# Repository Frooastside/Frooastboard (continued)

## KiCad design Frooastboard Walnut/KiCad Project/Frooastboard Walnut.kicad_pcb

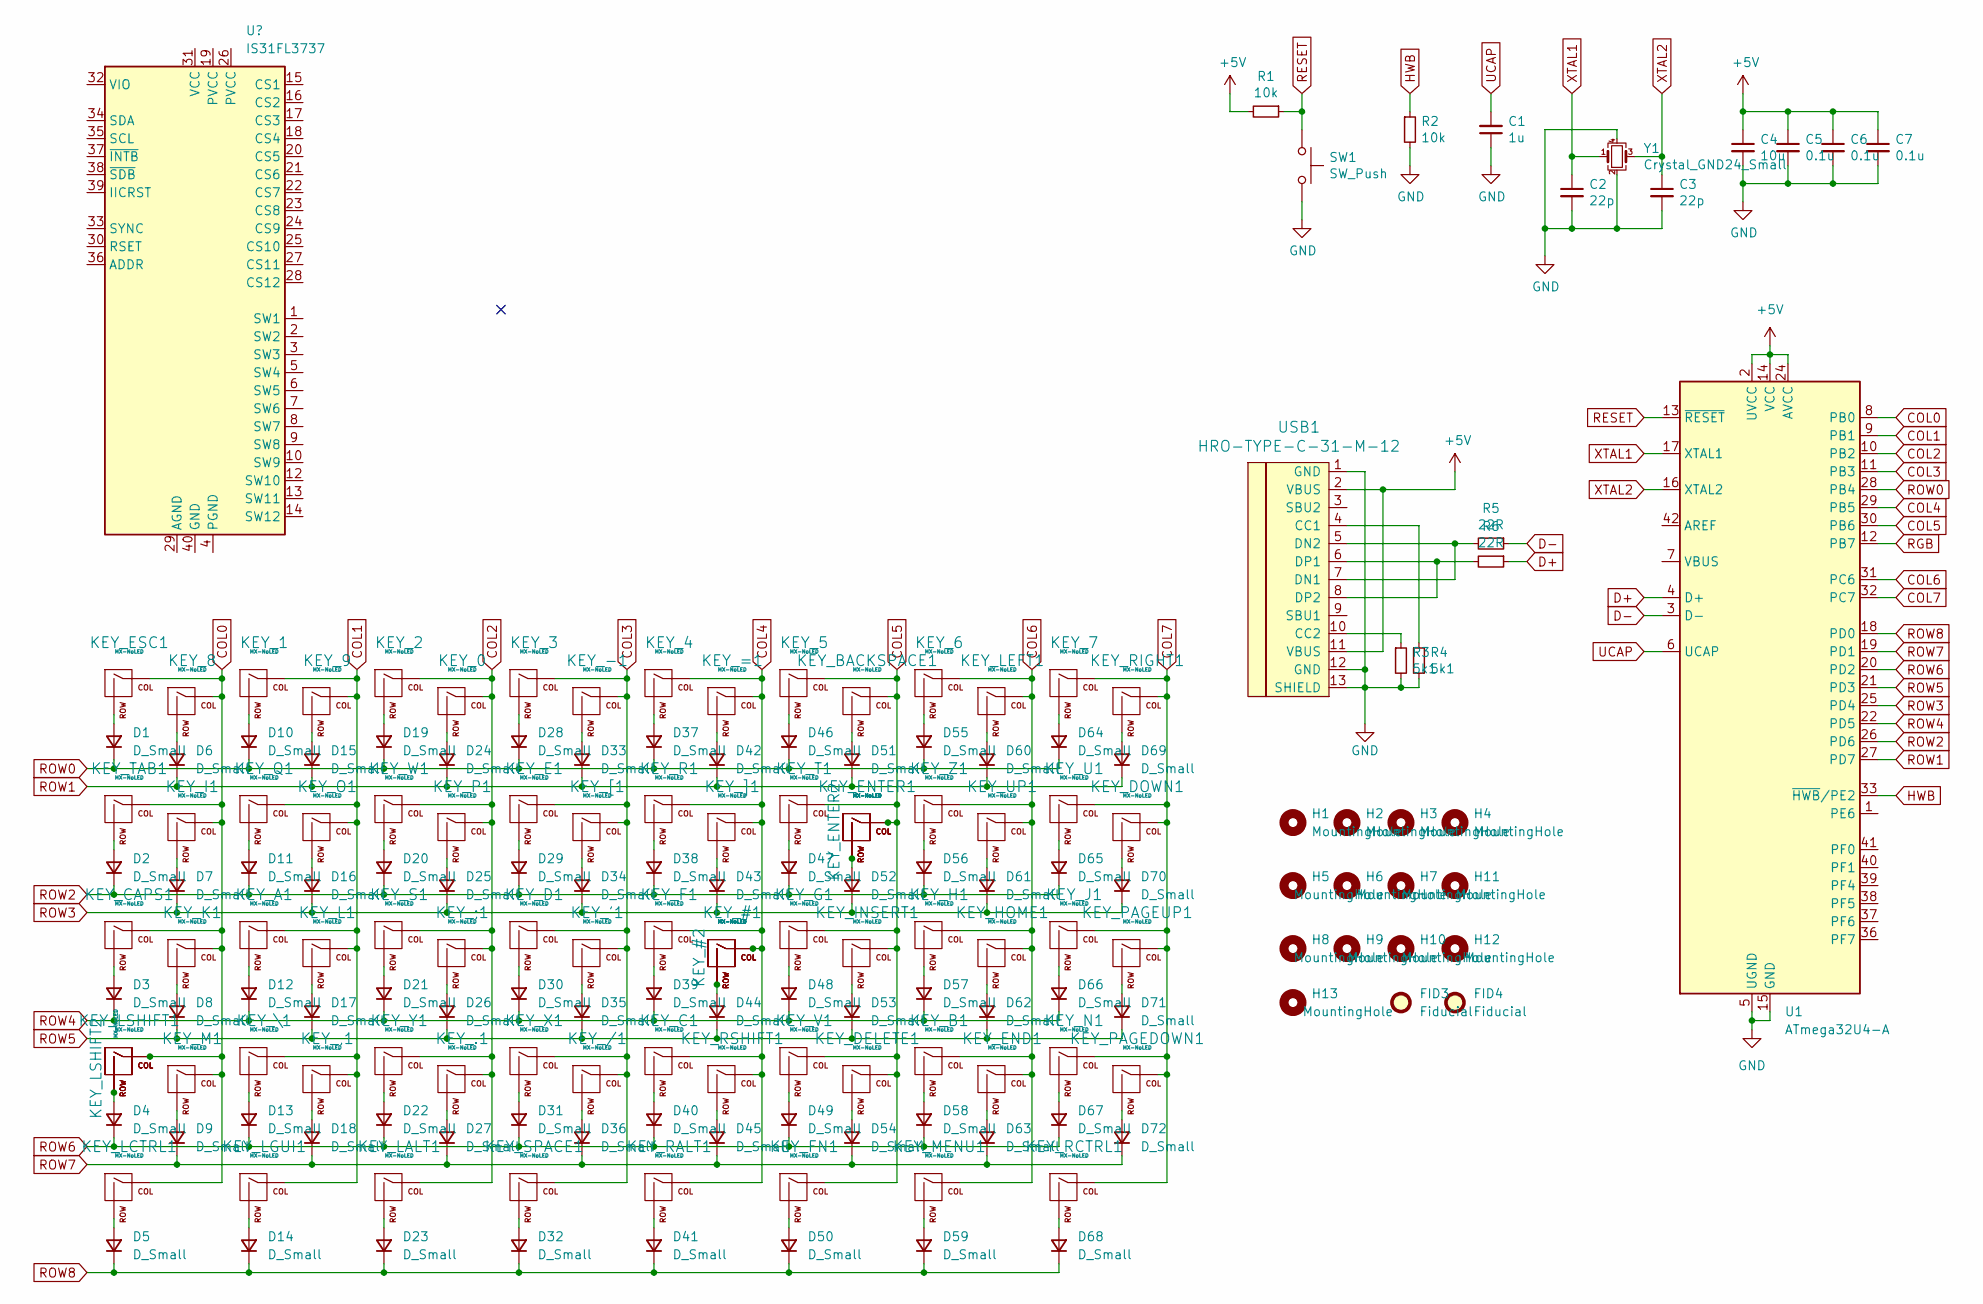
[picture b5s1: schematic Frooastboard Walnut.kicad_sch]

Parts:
C1: 1u; C_0805_2012Metric
C2, C3: 22p; C_0805_2012Metric
C4: 10u; C_0805_2012Metric
C5, C6, C7: 0.1u; C_0805_2012Metric
D1, D2, D3, D4, D5, D6, D7, D8, D9, D10, D11, D12, D13, D14, D15, D16, D17, D18, D19, D20, D21, D22, D23, D24, D25, D26, D27, D28, D29, D30, D31, D32, D33, D34, D35, D36, D37, D38, D39, D40, D41, D42, D43, D44, D45, D46, D47, D48, D49, D50, D51, D52, D53, D54, D55, D56, D57, D58, D59, D60, D61, D62, D63, D64, D65, D66, D67, D68, D69, D70, D71, D72: D_Small; D_0805_2012Metric
FID3, FID4: Fiducial; Fiducial_1mm_Mask2mm
H1, H2, H3, H4, H5, H6, H7, H8, H9, H10, H11, H12, H13: MountingHole; MountingHole_3.2mm_M3_DIN965
KEY_0, KEY_1, KEY_2, KEY_3, KEY_4, KEY_5, KEY_6, KEY_7, KEY_8, KEY_9, KEY_.1: MX-NoLED; MXOnly-1U-NoLED
KEY_#1: MX-NoLED; MXOnly-1U-NoLED
KEY_#2: MX-NoLED; MXOnly-1.5U-NoLED
KEY_'1: MX-NoLED; MXOnly-1U-NoLED
KEY_,1: MX-NoLED; MXOnly-1U-NoLED
KEY_-1: MX-NoLED; MXOnly-1U-NoLED
KEY_/1: MX-NoLED; MXOnly-1U-NoLED
KEY_;1: MX-NoLED; MXOnly-1U-NoLED
KEY_=1: MX-NoLED; MXOnly-1U-NoLED
KEY_A1: MX-NoLED; MXOnly-1U-NoLED
KEY_B1: MX-NoLED; MXOnly-1U-NoLED
KEY_BACKSPACE1: MX-NoLED; MXOnly-2U-NoLED
KEY_C1: MX-NoLED; MXOnly-1U-NoLED
KEY_CAPS1: MX-NoLED; MXOnly-1.75U-NoLED
KEY_D1: MX-NoLED; MXOnly-1U-NoLED
KEY_DELETE1: MX-NoLED; MXOnly-1U-NoLED
KEY_DOWN1: MX-NoLED; MXOnly-1U-NoLED
KEY_E1: MX-NoLED; MXOnly-1U-NoLED
KEY_END1: MX-NoLED; MXOnly-1U-NoLED
KEY_ENTER1: MX-NoLED; MXOnly-ISO-ROTATED-NoLED-NoStabilizers
KEY_ENTER2: MX-NoLED; MXOnly-2.25U-NoLED
KEY_ESC1: MX-NoLED; MXOnly-1U-NoLED
KEY_F1: MX-NoLED; MXOnly-1U-NoLED
KEY_FN1: MX-NoLED; MXOnly-1.25U-NoLED
KEY_G1: MX-NoLED; MXOnly-1U-NoLED
KEY_H1: MX-NoLED; MXOnly-1U-NoLED
KEY_HOME1: MX-NoLED; MXOnly-1U-NoLED
KEY_I1: MX-NoLED; MXOnly-1U-NoLED
KEY_INSERT1: MX-NoLED; MXOnly-1U-NoLED
KEY_J1: MX-NoLED; MXOnly-1U-NoLED
KEY_K1: MX-NoLED; MXOnly-1U-NoLED
KEY_L1: MX-NoLED; MXOnly-1U-NoLED
KEY_LALT1: MX-NoLED; MXOnly-1.25U-NoLED
KEY_LCTRL1: MX-NoLED; MXOnly-1.25U-NoLED
KEY_LEFT1: MX-NoLED; MXOnly-1U-NoLED
KEY_LGUI1: MX-NoLED; MXOnly-1.25U-NoLED
KEY_LSHIFT1: MX-NoLED; MXOnly-1.25U-NoLED
KEY_LSHIFT2: MX-NoLED; MXOnly-2.25U-NoLED
KEY_M1: MX-NoLED; MXOnly-1U-NoLED
KEY_MENU1: MX-NoLED; MXOnly-1.25U-NoLED
KEY_N1: MX-NoLED; MXOnly-1U-NoLED
KEY_O1: MX-NoLED; MXOnly-1U-NoLED
KEY_P1: MX-NoLED; MXOnly-1U-NoLED
KEY_PAGEDOWN1: MX-NoLED; MXOnly-1U-NoLED
KEY_PAGEUP1: MX-NoLED; MXOnly-1U-NoLED
KEY_Q1: MX-NoLED; MXOnly-1U-NoLED
KEY_R1: MX-NoLED; MXOnly-1U-NoLED
KEY_RALT1: MX-NoLED; MXOnly-1.25U-NoLED
KEY_RCTRL1: MX-NoLED; MXOnly-1.25U-NoLED
KEY_RIGHT1: MX-NoLED; MXOnly-1U-NoLED
KEY_RSHIFT1: MX-NoLED; MXOnly-2.75U-NoLED
KEY_S1: MX-NoLED; MXOnly-1U-NoLED
KEY_SPACE1: MX-NoLED; MXOnly-6.25U-NoLED
KEY_T1: MX-NoLED; MXOnly-1U-NoLED
KEY_TAB1: MX-NoLED; MXOnly-1.5U-NoLED
KEY_U1: MX-NoLED; MXOnly-1U-NoLED
KEY_UP1: MX-NoLED; MXOnly-1U-NoLED
KEY_V1: MX-NoLED; MXOnly-1U-NoLED
KEY_W1: MX-NoLED; MXOnly-1U-NoLED
KEY_X1: MX-NoLED; MXOnly-1U-NoLED
KEY_Y1: MX-NoLED; MXOnly-1U-NoLED
KEY_Z1: MX-NoLED; MXOnly-1U-NoLED
KEY_[1: MX-NoLED; MXOnly-1U-NoLED
KEY_\1: MX-NoLED; MXOnly-1U-NoLED
KEY_]1: MX-NoLED; MXOnly-1U-NoLED
R1, R2: 10k; R_0805_2012Metric
R3, R4: 5k1; R_0805_2012Metric
R5, R6: 22R; R_0805_2012Metric
SW1: SW_Push; SKQG-1155865
U1: ATmega32U4-A; QFN-44-1EP_7x7mm_P0.5mm_EP5.2x5.2mm
USB1: HRO-TYPE-C-31-M-12
Y1: Crystal_GND24_Small; Crystal_SMD_3225-4Pin_3.2x2.5mm

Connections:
+5V: C4.1, C5.1, C6.1, C7.1, R1.2, U1.2 (UVCC), U1.14 (VCC), U1.24 (AVCC), U1.34 (VCC), U1.44 (AVCC), USB1.2 (VBUS), USB1.11 (VBUS)
COL0: KEY_8.1 (COL), KEY_CAPS1.1 (COL), KEY_ESC1.1 (COL), KEY_I1.1 (COL), KEY_K1.1 (COL), KEY_LCTRL1.1 (COL), KEY_LSHIFT1.1 (COL), KEY_LSHIFT2.1 (COL), KEY_M1.1 (COL), KEY_TAB1.1 (COL), U1.8 (PB0)
COL1: KEY_1.1 (COL), KEY_9.1 (COL), KEY_,1.1 (COL), KEY_A1.1 (COL), KEY_L1.1 (COL), KEY_LGUI1.1 (COL), KEY_O1.1 (COL), KEY_Q1.1 (COL), KEY_\1.1 (COL), U1.9 (PB1)
COL2: KEY_0.1 (COL), KEY_2.1 (COL), KEY_.1.1 (COL), KEY_;1.1 (COL), KEY_LALT1.1 (COL), KEY_P1.1 (COL), KEY_S1.1 (COL), KEY_W1.1 (COL), KEY_Y1.1 (COL), U1.10 (PB2)
COL3: KEY_3.1 (COL), KEY_'1.1 (COL), KEY_-1.1 (COL), KEY_/1.1 (COL), KEY_D1.1 (COL), KEY_E1.1 (COL), KEY_SPACE1.1 (COL), KEY_X1.1 (COL), KEY_[1.1 (COL), U1.11 (PB3)
COL4: KEY_4.1 (COL), KEY_#1.1 (COL), KEY_#2.1 (COL), KEY_=1.1 (COL), KEY_C1.1 (COL), KEY_F1.1 (COL), KEY_R1.1 (COL), KEY_RALT1.1 (COL), KEY_RSHIFT1.1 (COL), KEY_]1.1 (COL), U1.29 (PB5)
COL5: KEY_5.1 (COL), KEY_BACKSPACE1.1 (COL), KEY_DELETE1.1 (COL), KEY_ENTER1.1 (COL), KEY_ENTER2.1 (COL), KEY_FN1.1 (COL), KEY_G1.1 (COL), KEY_INSERT1.1 (COL), KEY_T1.1 (COL), KEY_V1.1 (COL), U1.30 (PB6)
COL6: KEY_6.1 (COL), KEY_B1.1 (COL), KEY_END1.1 (COL), KEY_H1.1 (COL), KEY_HOME1.1 (COL), KEY_LEFT1.1 (COL), KEY_MENU1.1 (COL), KEY_UP1.1 (COL), KEY_Z1.1 (COL), U1.31 (PC6)
COL7: KEY_7.1 (COL), KEY_DOWN1.1 (COL), KEY_J1.1 (COL), KEY_N1.1 (COL), KEY_PAGEDOWN1.1 (COL), KEY_PAGEUP1.1 (COL), KEY_RCTRL1.1 (COL), KEY_RIGHT1.1 (COL), KEY_U1.1 (COL), U1.32 (PC7)
D+: R6.1, U1.4 (D+)
D-: R5.1, U1.3 (D-)
GND: C1.1, C2.2, C3.2, C4.2, C5.2, C6.2, C7.2, R2.2, R3.2, R4.2, SW1.2, U1.5 (UGND), U1.15 (GND), U1.23 (GND), U1.35 (GND), U1.43 (GND), USB1.1 (GND), USB1.12 (GND), USB1.13 (SHIELD), Y1.2, Y1.4
HWB: R2.1, U1.33 (~HWB/PE2)
unnamed: D1.2 (A), KEY_ESC1.2 (ROW)
unnamed: D2.2 (A), KEY_TAB1.2 (ROW)
unnamed: D3.2 (A), KEY_CAPS1.2 (ROW)
unnamed: D4.2 (A), KEY_LSHIFT1.2 (ROW), KEY_LSHIFT2.2 (ROW)
unnamed: D5.2 (A), KEY_LCTRL1.2 (ROW)
unnamed: D6.2 (A), KEY_8.2 (ROW)
unnamed: D7.2 (A), KEY_I1.2 (ROW)
unnamed: D8.2 (A), KEY_K1.2 (ROW)
unnamed: D9.2 (A), KEY_M1.2 (ROW)
unnamed: D10.2 (A), KEY_1.2 (ROW)
unnamed: D11.2 (A), KEY_Q1.2 (ROW)
unnamed: D12.2 (A), KEY_A1.2 (ROW)
unnamed: D13.2 (A), KEY_\1.2 (ROW)
unnamed: D14.2 (A), KEY_LGUI1.2 (ROW)
unnamed: D15.2 (A), KEY_9.2 (ROW)
unnamed: D16.2 (A), KEY_O1.2 (ROW)
unnamed: D17.2 (A), KEY_L1.2 (ROW)
unnamed: D18.2 (A), KEY_,1.2 (ROW)
unnamed: D19.2 (A), KEY_2.2 (ROW)
unnamed: D20.2 (A), KEY_W1.2 (ROW)
unnamed: D21.2 (A), KEY_S1.2 (ROW)
unnamed: D22.2 (A), KEY_Y1.2 (ROW)
unnamed: D23.2 (A), KEY_LALT1.2 (ROW)
unnamed: D24.2 (A), KEY_0.2 (ROW)
unnamed: D25.2 (A), KEY_P1.2 (ROW)
unnamed: D26.2 (A), KEY_;1.2 (ROW)
unnamed: D27.2 (A), KEY_.1.2 (ROW)
unnamed: D28.2 (A), KEY_3.2 (ROW)
unnamed: D29.2 (A), KEY_E1.2 (ROW)
unnamed: D30.2 (A), KEY_D1.2 (ROW)
unnamed: D31.2 (A), KEY_X1.2 (ROW)
unnamed: D32.2 (A), KEY_SPACE1.2 (ROW)
unnamed: D33.2 (A), KEY_-1.2 (ROW)
unnamed: D34.2 (A), KEY_[1.2 (ROW)
unnamed: D35.2 (A), KEY_'1.2 (ROW)
unnamed: D36.2 (A), KEY_/1.2 (ROW)
unnamed: D37.2 (A), KEY_4.2 (ROW)
unnamed: D38.2 (A), KEY_R1.2 (ROW)
unnamed: D39.2 (A), KEY_F1.2 (ROW)
unnamed: D40.2 (A), KEY_C1.2 (ROW)
unnamed: D41.2 (A), KEY_RALT1.2 (ROW)
unnamed: D42.2 (A), KEY_=1.2 (ROW)
unnamed: D43.2 (A), KEY_]1.2 (ROW)
unnamed: D44.2 (A), KEY_#1.2 (ROW), KEY_#2.2 (ROW)
unnamed: D45.2 (A), KEY_RSHIFT1.2 (ROW)
unnamed: D46.2 (A), KEY_5.2 (ROW)
unnamed: D47.2 (A), KEY_T1.2 (ROW)
unnamed: D48.2 (A), KEY_G1.2 (ROW)
unnamed: D49.2 (A), KEY_V1.2 (ROW)
unnamed: D50.2 (A), KEY_FN1.2 (ROW)
unnamed: D51.2 (A), KEY_BACKSPACE1.2 (ROW)
unnamed: D52.2 (A), KEY_ENTER1.2 (ROW), KEY_ENTER2.2 (ROW)
unnamed: D53.2 (A), KEY_INSERT1.2 (ROW)
unnamed: D54.2 (A), KEY_DELETE1.2 (ROW)
unnamed: D55.2 (A), KEY_6.2 (ROW)
unnamed: D56.2 (A), KEY_Z1.2 (ROW)
unnamed: D57.2 (A), KEY_H1.2 (ROW)
unnamed: D58.2 (A), KEY_B1.2 (ROW)
unnamed: D59.2 (A), KEY_MENU1.2 (ROW)
unnamed: D60.2 (A), KEY_LEFT1.2 (ROW)
unnamed: D61.2 (A), KEY_UP1.2 (ROW)
unnamed: D62.2 (A), KEY_HOME1.2 (ROW)
unnamed: D63.2 (A), KEY_END1.2 (ROW)
unnamed: D64.2 (A), KEY_7.2 (ROW)
unnamed: D65.2 (A), KEY_U1.2 (ROW)
unnamed: D66.2 (A), KEY_J1.2 (ROW)
unnamed: D67.2 (A), KEY_N1.2 (ROW)
unnamed: D68.2 (A), KEY_RCTRL1.2 (ROW)
unnamed: D69.2 (A), KEY_RIGHT1.2 (ROW)
unnamed: D70.2 (A), KEY_DOWN1.2 (ROW)
unnamed: D71.2 (A), KEY_PAGEUP1.2 (ROW)
unnamed: D72.2 (A), KEY_PAGEDOWN1.2 (ROW)
unnamed: R3.1, USB1.10 (CC2)
unnamed: R4.1, USB1.4 (CC1)
unnamed: R5.2, USB1.5 (DN2), USB1.7 (DN1)
unnamed: R6.2, USB1.6 (DP1), USB1.8 (DP2)
RESET: R1.1, SW1.1, U1.13 (~RESET)
RGB: U1.12 (PB7)
ROW0: D1.1 (K), D10.1 (K), D19.1 (K), D28.1 (K), D37.1 (K), D46.1 (K), D55.1 (K), D64.1 (K), U1.28 (PB4)
ROW1: D6.1 (K), D15.1 (K), D24.1 (K), D33.1 (K), D42.1 (K), D51.1 (K), D60.1 (K), D69.1 (K), U1.27 (PD7)
ROW2: D2.1 (K), D11.1 (K), D20.1 (K), D29.1 (K), D38.1 (K), D47.1 (K), D56.1 (K), D65.1 (K), U1.26 (PD6)
ROW3: D7.1 (K), D16.1 (K), D25.1 (K), D34.1 (K), D43.1 (K), D52.1 (K), D61.1 (K), D70.1 (K), U1.25 (PD4)
ROW4: D3.1 (K), D12.1 (K), D21.1 (K), D30.1 (K), D39.1 (K), D48.1 (K), D57.1 (K), D66.1 (K), U1.22 (PD5)
ROW5: D8.1 (K), D17.1 (K), D26.1 (K), D35.1 (K), D44.1 (K), D53.1 (K), D62.1 (K), D71.1 (K), U1.21 (PD3)
ROW6: D4.1 (K), D13.1 (K), D22.1 (K), D31.1 (K), D40.1 (K), D49.1 (K), D58.1 (K), D67.1 (K), U1.20 (PD2)
ROW7: D9.1 (K), D18.1 (K), D27.1 (K), D36.1 (K), D45.1 (K), D54.1 (K), D63.1 (K), D72.1 (K), U1.19 (PD1)
ROW8: D5.1 (K), D14.1 (K), D23.1 (K), D32.1 (K), D41.1 (K), D50.1 (K), D59.1 (K), D68.1 (K), U1.18 (PD0)
UCAP: C1.2, U1.6 (UCAP)
XTAL1: C2.1, U1.17 (XTAL1), Y1.1
XTAL2: C3.1, U1.16 (XTAL2), Y1.3

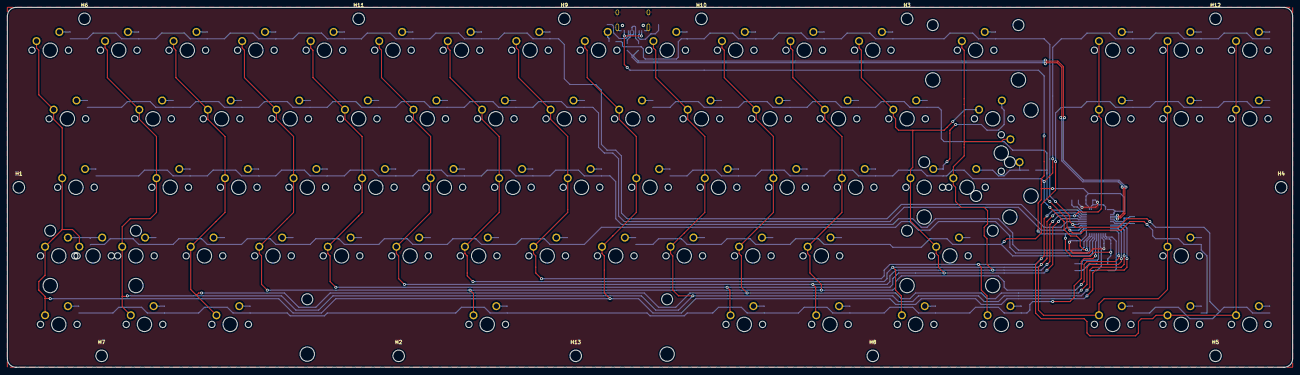
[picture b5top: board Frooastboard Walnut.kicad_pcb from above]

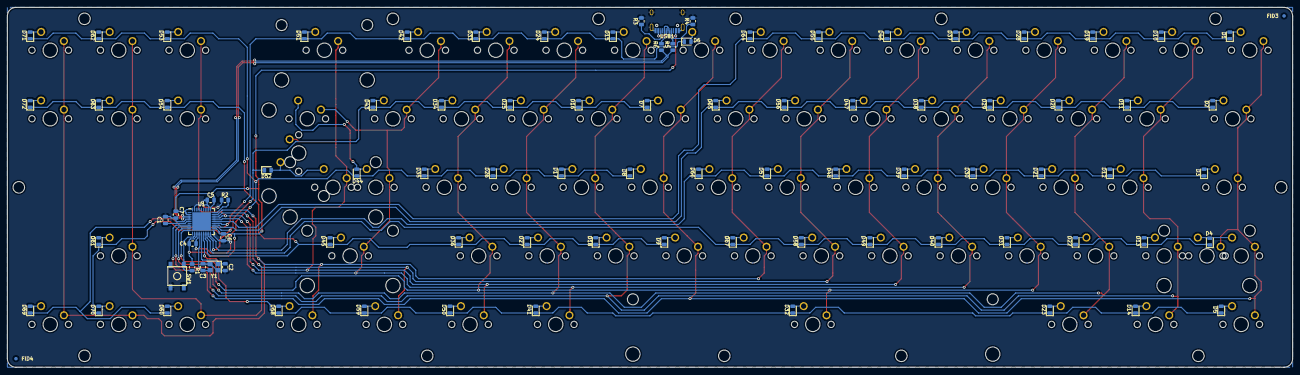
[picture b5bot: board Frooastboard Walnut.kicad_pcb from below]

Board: 2 copper layers, 357.2 x 100.0 mm, 179 parts (91 on the bottom side), 102 nets.

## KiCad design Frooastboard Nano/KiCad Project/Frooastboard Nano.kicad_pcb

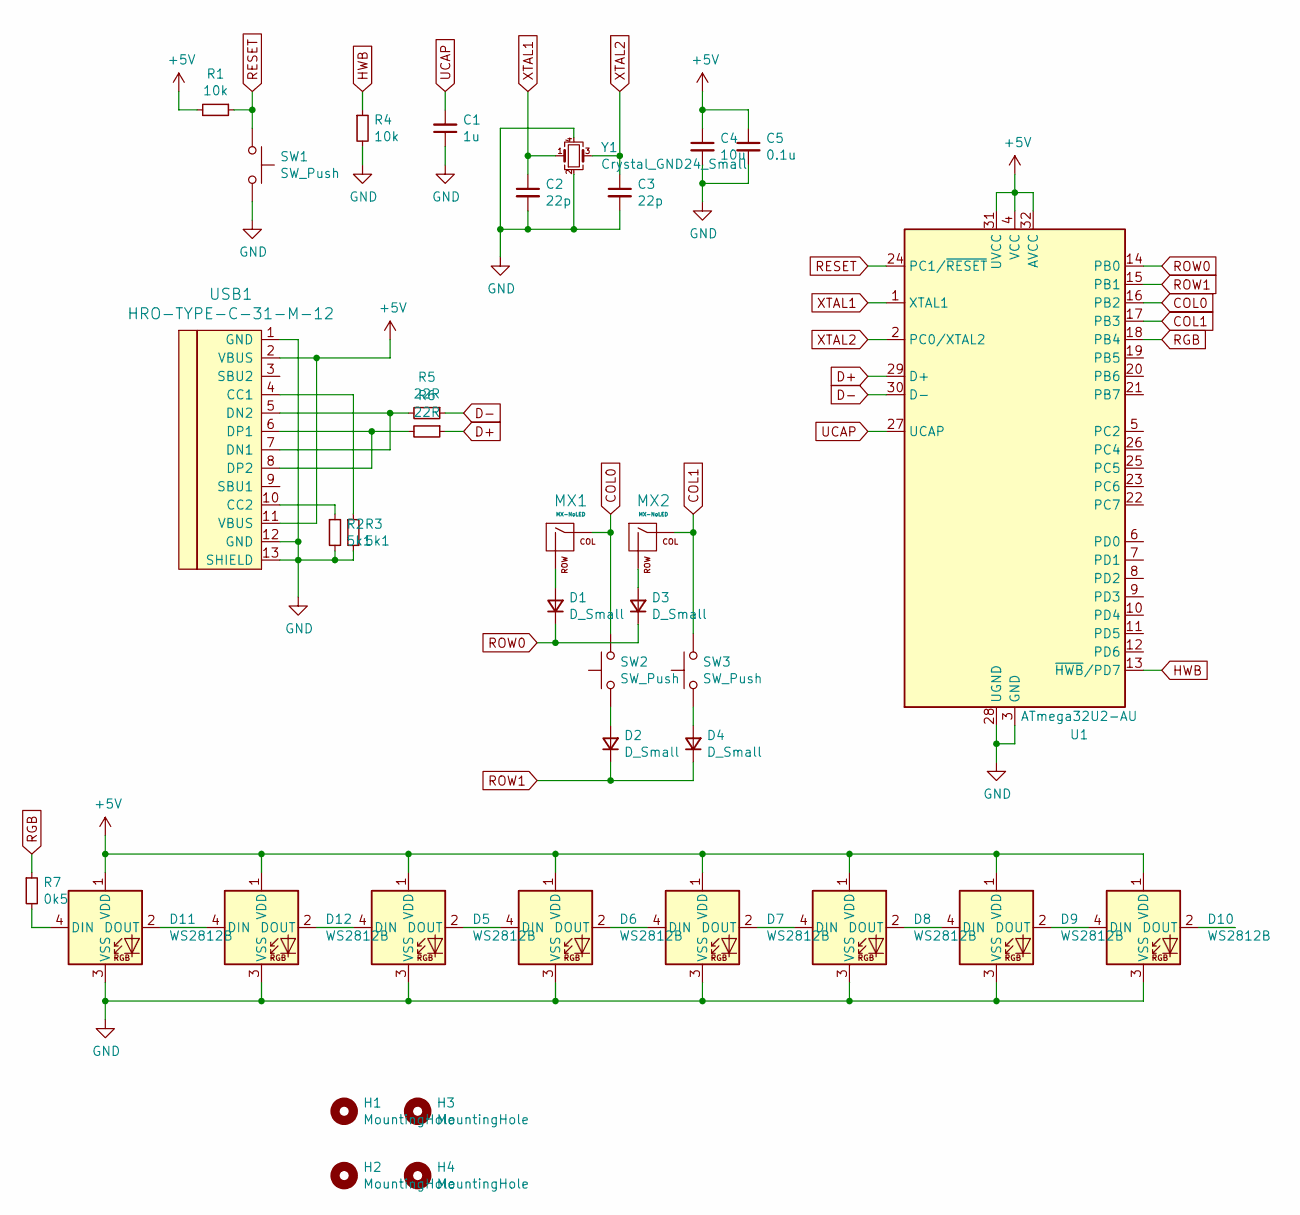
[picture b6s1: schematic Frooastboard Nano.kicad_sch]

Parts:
C1: 1u; C_0805_2012Metric
C2, C3: 22p; C_0805_2012Metric
C4: 10u; C_0805_2012Metric
C5: 0.1u; C_0805_2012Metric
D1, D2, D3, D4: D_Small; D_0805_2012Metric
D5, D6, D7, D8, D9, D10, D11, D12: WS2812B; LED_WS2812B_PLCC4_5.0x5.0mm_P3.2mm
H1, H2, H3, H4: MountingHole; MountingHole_2.7mm_M2.5_DIN965
MX1, MX2: MX-NoLED; MXOnly-1U-NoLED
R1, R4: 10k; R_0805_2012Metric
R2, R3: 5k1; R_0805_2012Metric
R5, R6: 22R; R_0805_2012Metric
R7: 0k5; R_0805_2012Metric
SW1, SW2, SW3: SW_Push; SKQG-1155865
U1: ATmega32U2-AU; TQFP-32_7x7mm_P0.8mm
USB1: HRO-TYPE-C-31-M-12
Y1: Crystal_GND24_Small; Crystal_SMD_3225-4Pin_3.2x2.5mm

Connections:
+5V: C4.1, C5.1, D5.1 (VDD), D6.1 (VDD), D7.1 (VDD), D8.1 (VDD), D9.1 (VDD), D10.1 (VDD), D11.1 (VDD), D12.1 (VDD), R1.2, U1.4 (VCC), U1.31 (UVCC), U1.32 (AVCC), USB1.2 (VBUS), USB1.11 (VBUS)
COL0: MX1.1 (COL), SW2.2, U1.16 (PB2)
COL1: MX2.1 (COL), SW3.2, U1.17 (PB3)
D+: R6.1, U1.29 (D+)
D-: R5.1, U1.30 (D-)
GND: C1.1, C2.2, C3.2, C4.2, C5.2, D5.3 (VSS), D6.3 (VSS), D7.3 (VSS), D8.3 (VSS), D9.3 (VSS), D10.3 (VSS), D11.3 (VSS), D12.3 (VSS), R2.2, R3.2, R4.2, SW1.2, U1.3 (GND), U1.28 (UGND), USB1.1 (GND), USB1.12 (GND), USB1.13 (SHIELD), Y1.2, Y1.4
HWB: R4.1, U1.13 (~HWB/PD7)
unnamed: D1.2 (A), MX1.2 (ROW)
unnamed: D2.2 (A), SW2.1
unnamed: D3.2 (A), MX2.2 (ROW)
unnamed: D4.2 (A), SW3.1
unnamed: D5.2 (DOUT), D6.4 (DIN)
unnamed: D6.2 (DOUT), D7.4 (DIN)
unnamed: D7.2 (DOUT), D8.4 (DIN)
unnamed: D8.2 (DOUT), D9.4 (DIN)
unnamed: D9.2 (DOUT), D10.4 (DIN)
unnamed: D11.2 (DOUT), D12.4 (DIN)
unnamed: D11.4 (DIN), R7.2
unnamed: D5.4 (DIN), D12.2 (DOUT)
unnamed: R2.1, USB1.10 (CC2)
unnamed: R3.1, USB1.4 (CC1)
unnamed: R5.2, USB1.5 (DN2), USB1.7 (DN1)
unnamed: R6.2, USB1.6 (DP1), USB1.8 (DP2)
RESET: R1.1, SW1.1, U1.24 (PC1/~RESET)
RGB: R7.1, U1.18 (PB4)
ROW0: D1.1 (K), D3.1 (K), U1.14 (PB0)
ROW1: D2.1 (K), D4.1 (K), U1.15 (PB1)
UCAP: C1.2, U1.27 (UCAP)
XTAL1: C2.1, U1.1 (XTAL1), Y1.1
XTAL2: C3.1, U1.2 (PC0/XTAL2), Y1.3

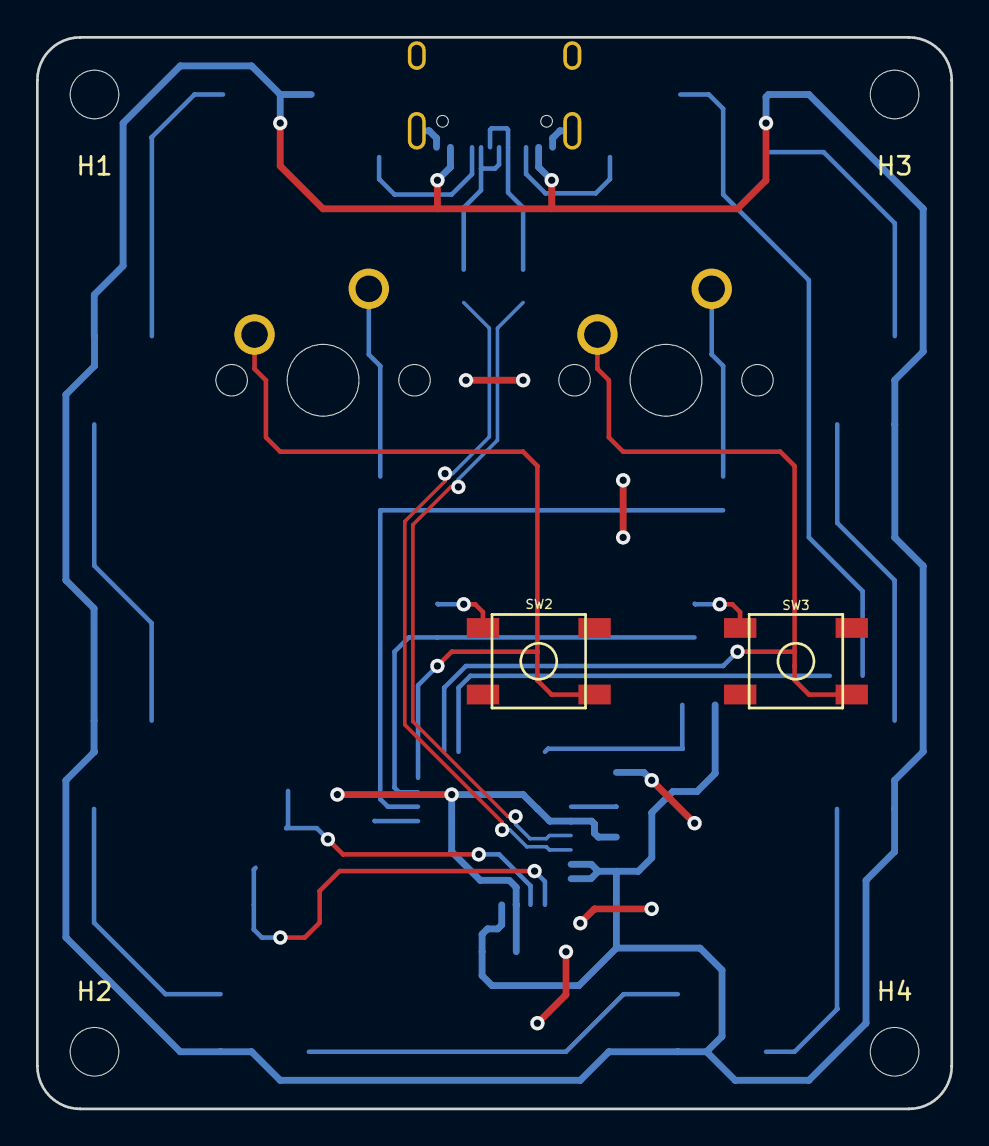
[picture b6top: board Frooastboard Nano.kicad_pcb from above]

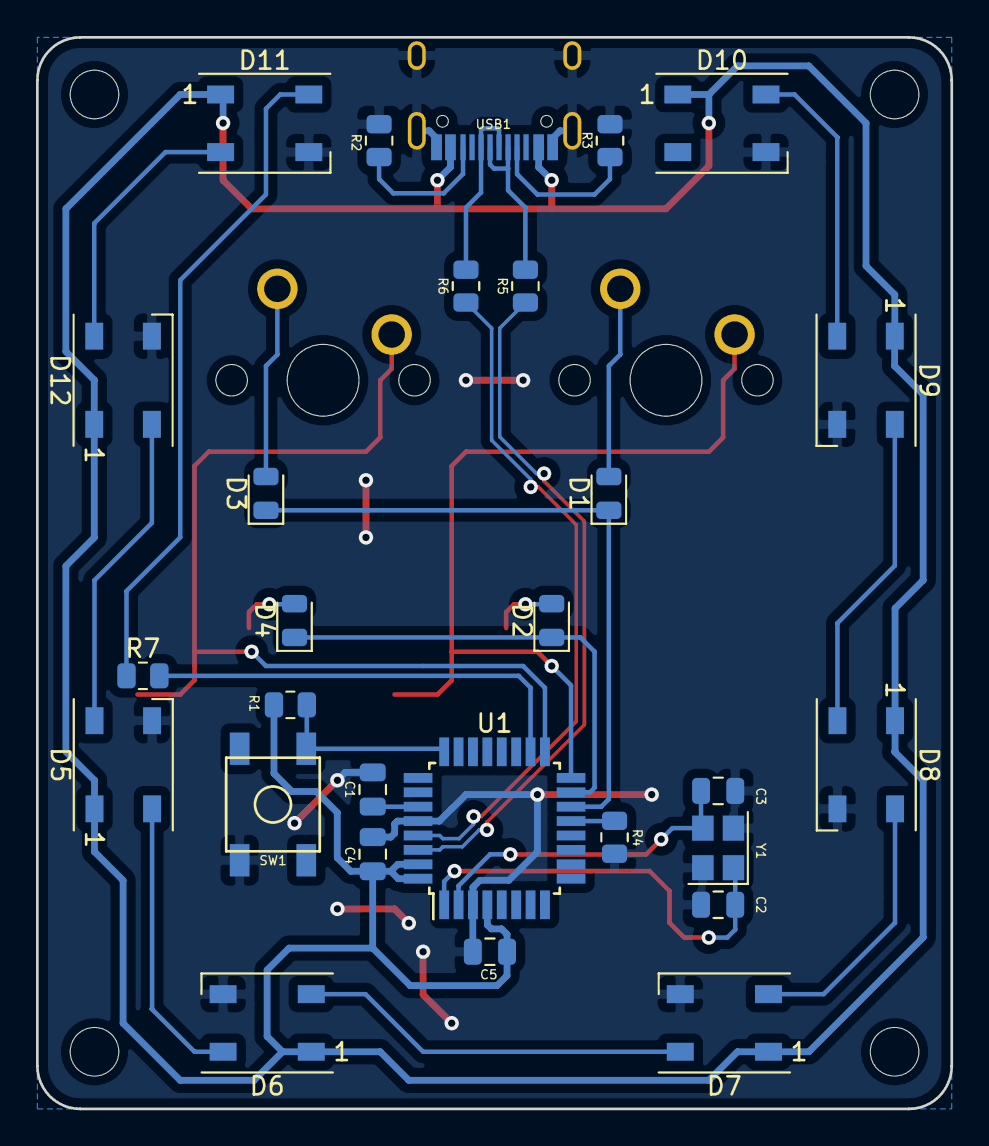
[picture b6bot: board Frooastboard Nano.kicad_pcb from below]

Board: 2 copper layers, 50.8 x 59.5 mm, 36 parts (28 on the bottom side), 30 nets.

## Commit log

2021-05-31 complete rewiring
2021-06-03 sdfsdsdssdsdsssssdsds
2021-06-03 update alles so catia und teile
2021-06-04 gerber
2021-06-04 gerber fixed drill hole naming
2021-06-04 Gerber with ground lines added
2021-06-06 kaufen
2022-02-16 Add Frooastboard Walnut
2022-02-16 backup
2022-02-16 Finished Basic Layout
2022-02-16 tqfp -> qfn
2022-02-17 fix drc errors
2022-02-17 rename keys
2022-02-17 gerber files
2022-02-17 remove gerber files from main directory
2022-02-18 basic implementation on schematic
2022-02-18 space for leds
2022-02-18 driver placement
2022-02-18 annotation
2022-02-20 iso ansi support
    Schematic: Switches are double stacked!
2022-02-20 drill marker
2022-02-20 Move screw hole
2022-02-20 Basic Frame
2022-02-20 Update MX_Alps_Hybrid
2022-02-22 Bottom Row
2022-02-22 second row
2022-02-22 middle row
2022-02-22 rotate iso enter switch
2022-02-23 2U Stabilizer
2022-02-23 6.25U Stabilizer
2022-02-23 Mounting Holes
2022-02-23 Muttern
2022-02-23 idk?
2022-02-24 Switch Clips
2022-02-26 smd rgb led
2022-02-26 led schematic
2022-02-26 LED Placement
2022-02-26 switch leds
2022-02-27 all 3-bundles
2022-02-28 spacing
2022-02-28 finished?
2022-02-28 final pcb rev1
2022-03-01 usb buchse
2022-03-06 change to relative path
2022-03-20 fix vbus connection
2022-03-20 generate new gerber files
2022-03-24 update trace thickness and add tantalum
2022-03-24 add b
2022-03-25 flip space stabilizer
2022-03-25 finished deckel
2022-03-25 leds
2022-03-25 Fertig
2022-03-25 alles
2022-03-26 fix 12.* to 11.906
2022-03-27 fix screw holes and double line
2022-03-28 Holzdeckel dxf
2022-03-28 holzdeckel
2022-03-28 Holzdeckel sheetcam job and part
2022-04-18 add various parts to lib
2022-04-18 add frooastboard walnut modular draft
2022-07-23 assign some footprints
2022-10-05 Switch to IP2312
2022-10-09 do some stuff
2022-10-09 almost finish schematic
2022-10-10 before nrf52810
2022-10-12 some new stuff
2022-10-13 asign pieces
2022-10-15 some backup
2022-10-15 some settings
2022-10-15 prepare
2022-10-15 antenna
2022-10-15 do some stuff (probably redo that)
2022-10-16 mmmhhh rp2040
2022-11-22 is chip
2022-11-23 rearange some stuff
2022-12-16 stuff
2023-05-02 update file version
2023-05-04 update headers
2023-05-04 more footprint changes
2023-06-20 change some stuff maybe finally get started
2023-06-21 some errors and board outline
2023-06-21 some more stuff changed
2023-06-23 some more progress
2023-06-26 Main Module placement
2023-06-26 basic left side
2023-06-26 backup before differential
2023-06-26 basically done
2023-06-26 more stuff little weird
2023-06-26 some more stuff
2023-06-29 some updates
2023-06-29 before moving stuff
2023-06-29 somewhat good
2023-06-29 outlines
2023-07-19 probably like done
2023-07-19 remove weird edge
2023-07-24 some stuff
2023-07-25 remove lockfile
2023-07-25 tiling
2023-07-25 import mm2040
2023-07-26 some stuff and caps lock
2023-08-01 all keys placed
2023-08-01 some leds and stuff
2023-08-01 fix some issues
2023-08-02 updates or something like that
2023-08-05 actually place leds good
2023-08-06 add AFA01-SXXFCX-00 lib
2023-08-07 fix symbols and remove lck
2023-08-07 fix drc erc errors
2023-08-07 almost finished bus stuff connector fpc
2023-08-08 power symbols
2023-08-08 add reset pin
2023-08-08 update reference multi leds
2023-08-08 idk some updates
2023-08-10 update fpc library
2023-08-10 update library references
2023-08-11 update pad numbers
2023-08-11 update leds and diodes
2023-08-11 flip footprint to back for clearence
2023-08-11 update to 2 layer pcb
2023-09-13 make sure bottom and top are always connected
2023-09-17 fix errors
2023-09-17 i probably will revert this
2023-11-26 i have no idea
2024-04-10 A600
2024-04-11 more led stuff NOT REVERSED YET
2024-04-12 new leds (finally)
2024-04-17 change export settings
2024-04-17 Add Ground Plane
2024-04-30 bug fixes
2024-04-30 update afa24 pos
2024-05-03 move ralt
2024-05-06 AFA24
2024-05-15 all keycaps placed
2024-05-15 shapes
2024-05-15 fixed?
2024-05-15 first line
2024-05-17 some more stuff ig
2024-05-17 fix 4pin (other still wrong)
2024-05-20 arrows
2024-05-22 before double a
2024-05-22 almost final
2024-05-23 font
2024-05-25 size updates
2024-05-25 lock
2024-06-03 make more space on the edges
2024-06-05 add basic german
2024-06-05 prepare for pcba
2024-06-19 british
2024-06-19 cutout
2024-06-19 idk lock layers and stuff
2024-07-08 plate and afa01
2024-07-08 roof and a
2024-07-09 make 3mm hole actually 3mm on all layers
2024-12-08 move resistor for easy led access
    also move to linux
2024-12-10 fix large unnecessary holes
2024-12-10 iso rotated key
2024-12-10 Remove A600 from public repository
